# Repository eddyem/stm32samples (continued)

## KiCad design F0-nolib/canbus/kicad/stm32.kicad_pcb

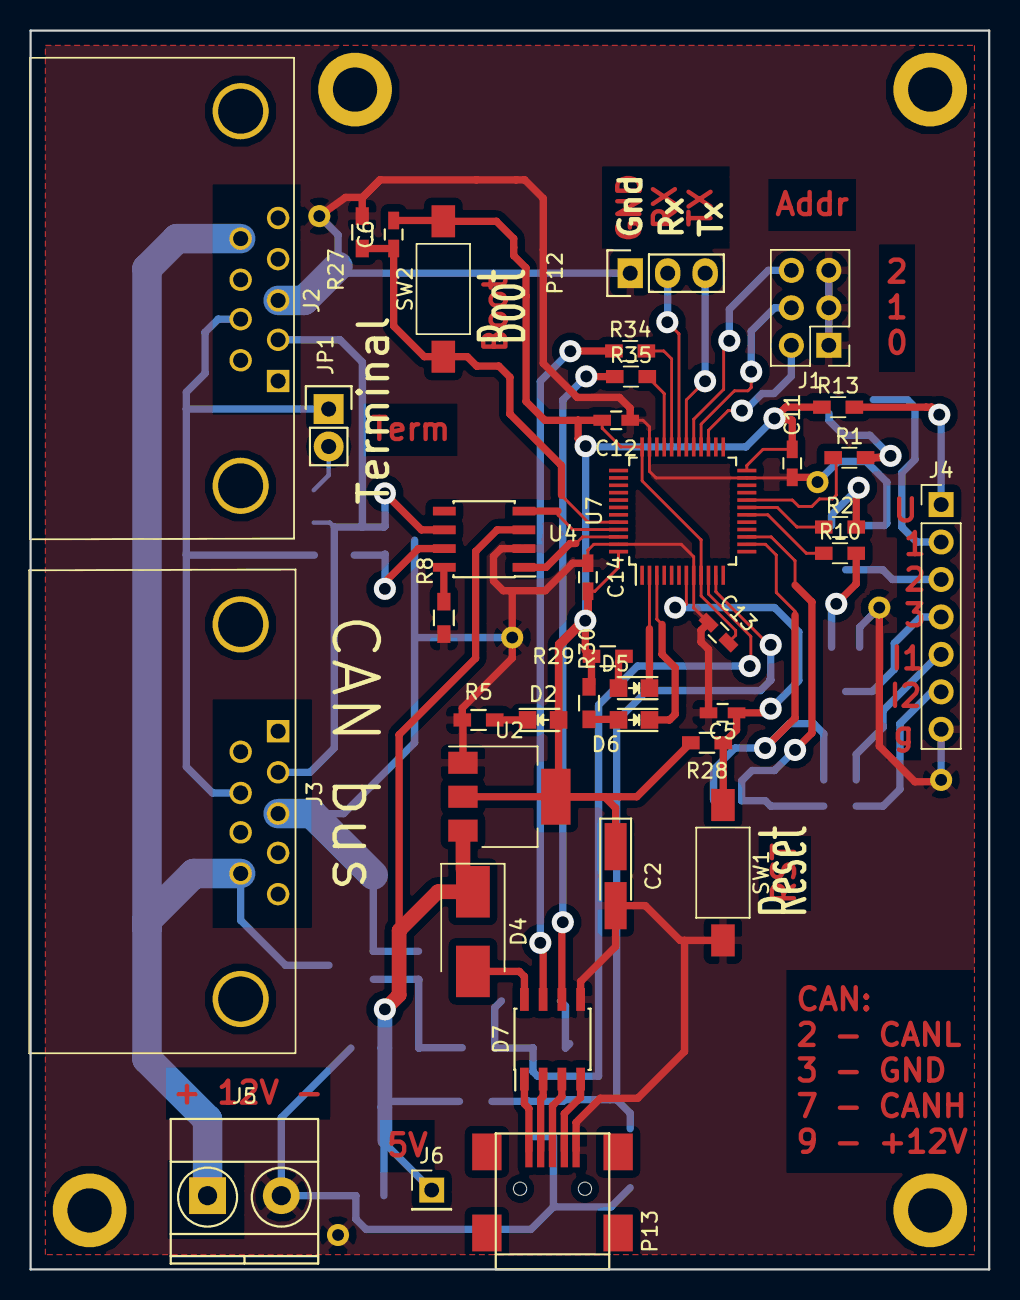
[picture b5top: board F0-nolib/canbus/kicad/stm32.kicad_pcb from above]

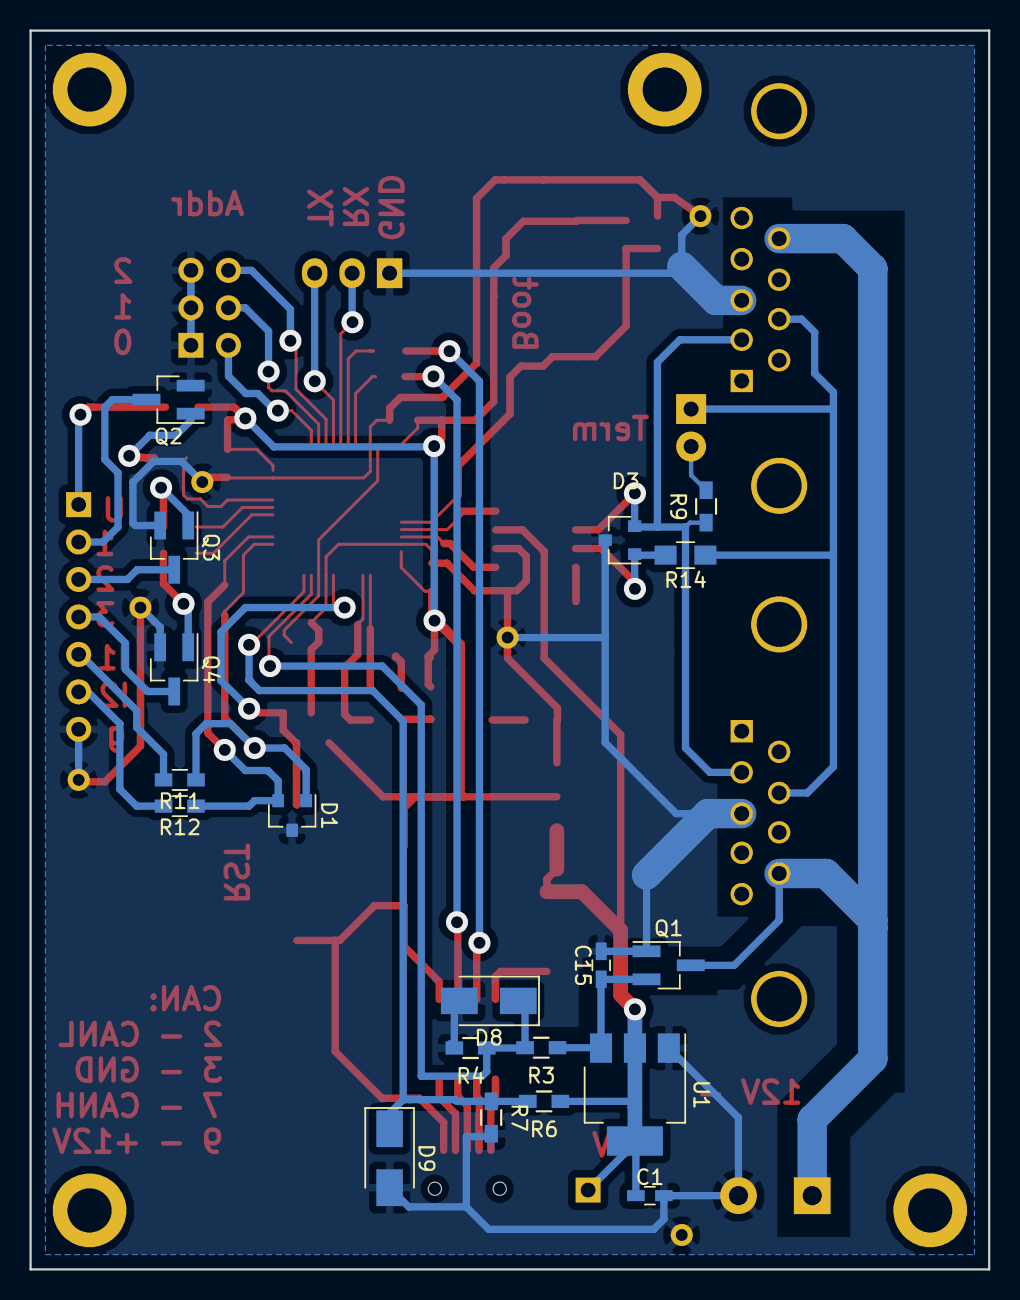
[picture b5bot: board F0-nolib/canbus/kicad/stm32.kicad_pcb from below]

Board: 2 copper layers, 65.0 x 84.0 mm, 61 parts (19 on the bottom side), 49 nets.

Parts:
C1, C5, C6, C11, C12, C13, C14, C15: 0.1; C_0603_HandSoldering
C2: 47u; Tantalum_Case-A_EIA-3216-18_Hand
D1: SP0502BAHT; SOT-23
D2: LED; LED_0805
D3: PESD1CAN; SOT-23
D4: MBRS130L; D_SMB_Handsoldering
D5: LED0; LED_0805
D6: LED1; LED_0805
D7: USB6B1; SOIC-8_3.9x4.9mm_Pitch1.27mm
D8, D9: SMAJ5.0A; D_SMA
J1: CONN_02X03; Pin_Header_Straight_2x03_Pitch2.54mm
J2: DB9_Female; DB9FC
J3: DB9_Male; DB9MC
J4: Conn_01x07; Pin_Header_Straight_1x07_Pitch2.54mm
J5: 12v; TerminalBlock_Pheonix_MKDS1.5-2pol
J6: Conn_01x01; Pin_Header_Straight_1x01_Pitch2.54mm
JP1: Terminal; Pin_Header_Straight_1x02
P12: USART_BOOT; Pin_Header_Straight_1x03
P13: USB_A; USB_Mini-B
P15, P16, P17, P18: Hole; Hole_3mm
Q1: AO3407; SOT-23_Handsoldering
Q2, Q3, Q4: SI2300; SOT-23_Handsoldering
R1, R2, R5, R10, R11, R12, R29, R30: 330; R_0603_HandSoldering
R3: 220k; R_0603_HandSoldering
R4: 56k; R_0603_HandSoldering
R6, R7: 47k; R_0603_HandSoldering
R8: 4k7; R_0603_HandSoldering
R9: 120; R_0603_HandSoldering
R13: 4.7; R_0603_HandSoldering
R14: 0; R_0805_HandSoldering
R27, R28: 10k; R_0603_HandSoldering
R34, R35: 22; R_0603_HandSoldering
SW1: Reset; SW_SPST_FSMSM
SW2: Boot; SW_SPST_FSMSM
U1: LM1117-5.0; SOT-223
U2: LM1117-3.3; SOT-223
U4: MCP2551-I/SN; SOIC-8_3.9x4.9mm_Pitch1.27mm
U7: STM32F042C6Tx; LQFP-48_7x7mm_Pitch0.5mm

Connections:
+3V3: C2.1, C6.2, C11.2, C12.2, C13.2, C14.2, D2.2, R13.1, R28.2, R29.2, R30.2, SW2.2, U2.2, U2.4, U7.9, U7.24, U7.36, U7.48
+5V: C1.1, D4.1, J6.1, R6.1, U1.2, U1.4, U2.3, U4.3
/5Vusb: D4.2, D7.8
/12Vin: C15.1, Q1.2, R3.1, U1.3
/BOOT0: C6.1, R27.1, SW2.1, U7.44
/CAN_Rx: U4.4, U7.45
/CAN_Tx: U4.1, U7.46
/INP1: D1.1, R11.1, U7.14
/INP2: D1.2, R12.1, U7.15
/LED0: D5.1, U7.2
/LED1: D6.1, U7.3
/NRST: C5.1, R28.1, SW1.1, U7.7
/O1: R1.1, U7.20
/O2: R2.1, U7.19
/O3: R10.1, U7.18
/OUTP1: J4.2, Q2.3
/OUTP2: J4.3, Q3.3
/OUTP3: J4.4, Q4.3
/Rx: P12.2, U7.31
/Tx: P12.3, U7.30
/V5: D9.1, R6.2, R7.1, U7.11
/V12: D8.1, R3.2, R4.1, U7.10
/brdaddr0: J1.2, U7.27
/brdaddr1: J1.4, U7.28
/brdaddr2: J1.6, U7.29
GND: C1.2, C2.2, C5.2, C11.1, C12.1, C13.1, C14.1, C15.2, D1.3, D3.3, D7.5, D8.2, D9.2, J1.1, J1.3, J1.5, J2.3, J3.3, J4.7, J5.2, P12.1, P13.5, Q1.1, Q2.2, Q3.2, Q4.2, R4.2, R5.1, R7.2, R8.2, R27.2, SW1.2, U1.1, U2.1, U4.2, U7.8, U7.23, U7.35, U7.47
unnamed: D2.1, R5.2
unnamed: D3.1, R14.2, U4.7
unnamed: D3.2, J2.2, J3.2, R9.1, U4.6
unnamed: D5.2, R29.1
unnamed: D6.2, R30.1
unnamed: D7.1, P13.1
unnamed: D7.2, P13.2
unnamed: D7.3, P13.3
unnamed: D7.4, P13.4
unnamed: D7.6, R35.1
unnamed: D7.7, R34.1
unnamed: J2.7, J3.7, JP1.1, R14.1
unnamed: J2.9, J3.9, J5.1, Q1.3
unnamed: J4.1, R13.2
unnamed: J4.5, R11.2
unnamed: J4.6, R12.2
unnamed: JP1.2, R9.2
unnamed: Q2.1, R1.2
unnamed: Q3.1, R2.2
unnamed: Q4.1, R10.2
unnamed: R8.1, U4.8
unnamed: R34.2, U7.32
unnamed: R35.2, U7.33

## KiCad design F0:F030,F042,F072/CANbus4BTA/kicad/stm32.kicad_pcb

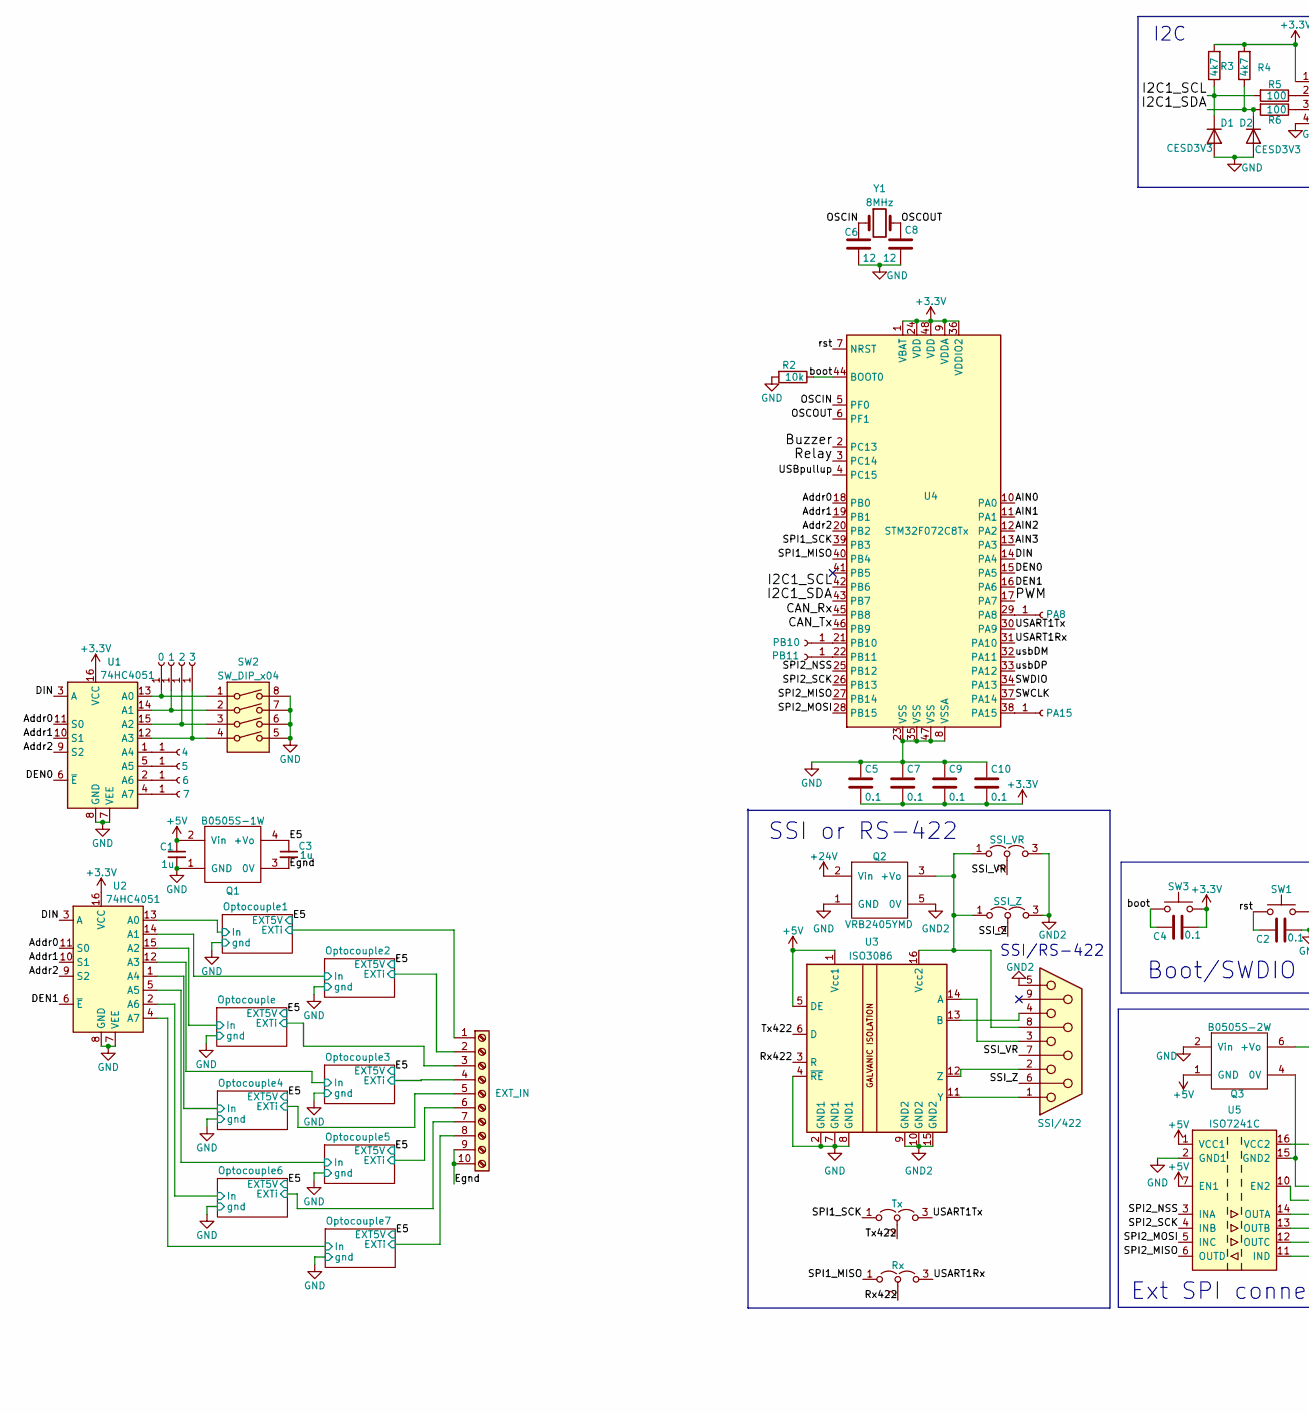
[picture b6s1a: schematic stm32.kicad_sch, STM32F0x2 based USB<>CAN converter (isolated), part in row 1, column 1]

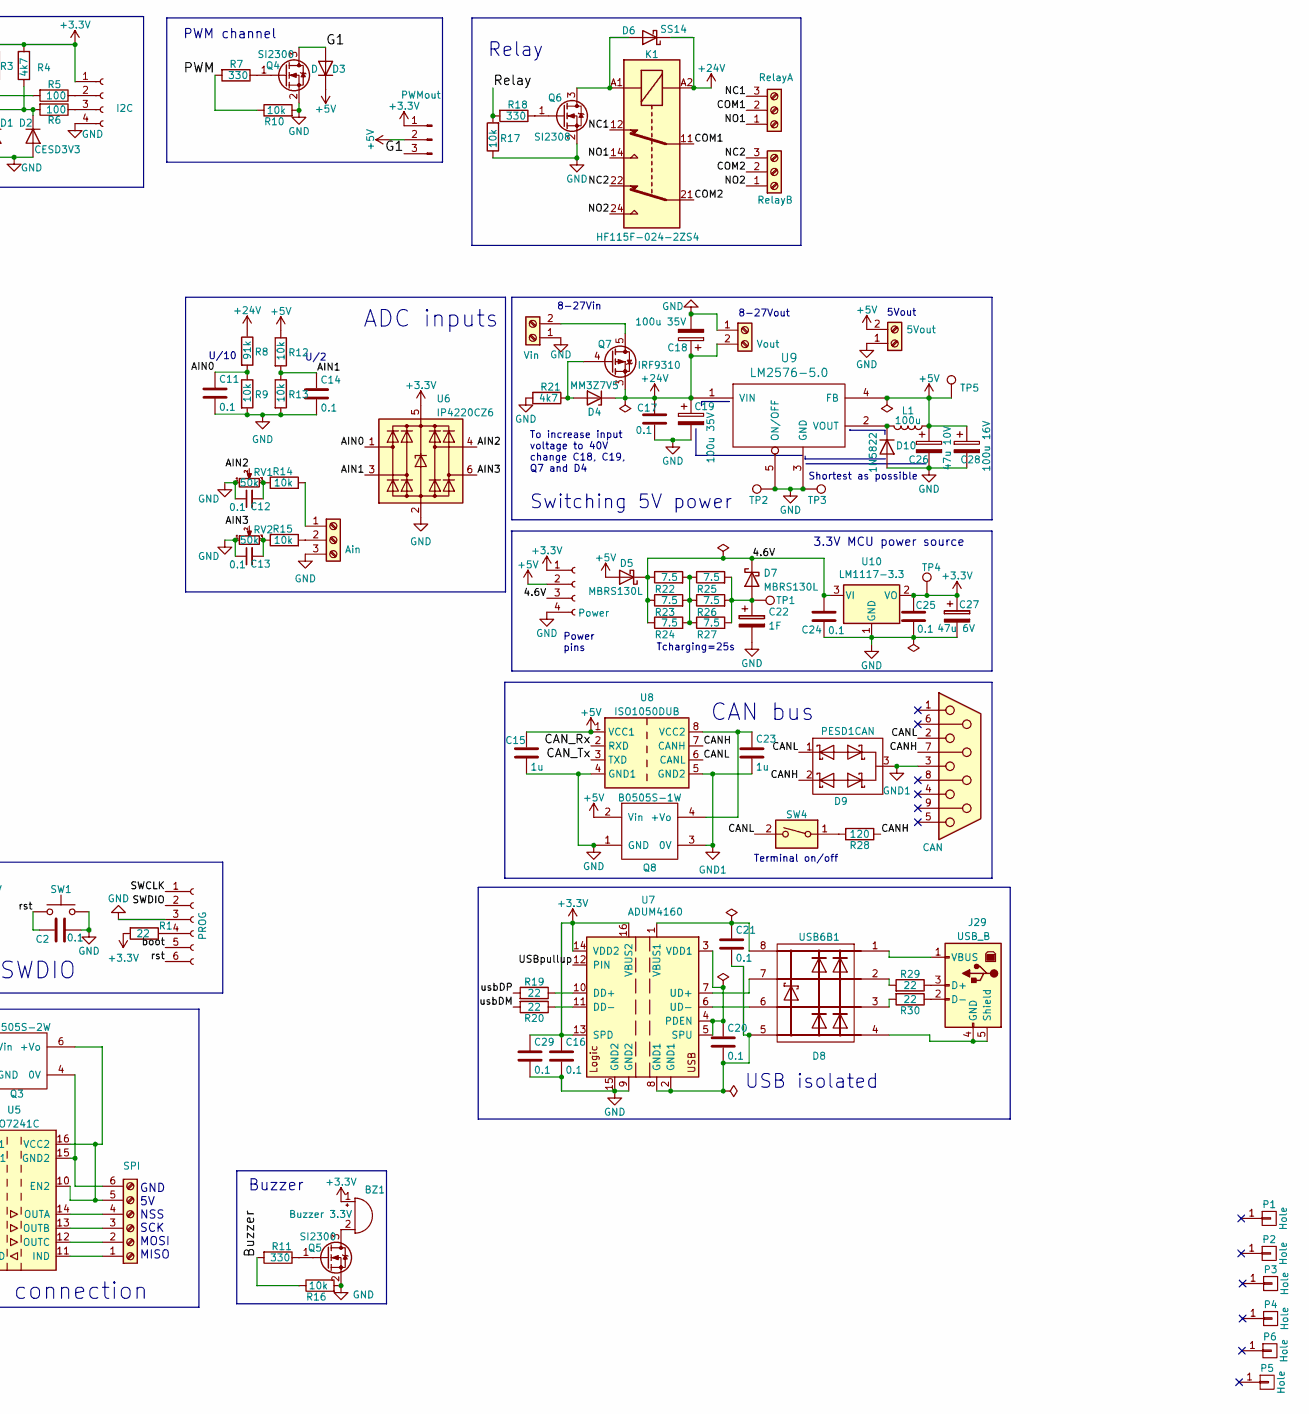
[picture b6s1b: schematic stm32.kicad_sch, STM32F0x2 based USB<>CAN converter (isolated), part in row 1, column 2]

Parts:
BZ1: Buzzer 3.3V; Buzzer_12x9.5RM7.6
C1, C3, C15, C23: 1u; C_0805_2012Metric_Pad1.18x1.45mm_HandSolder
C2, C4, C5, C7, C9, C10, C11, C12, C13, C14, C16, C17, C20, C21, C24, C25, C29: 0.1; C_0603_1608Metric_Pad1.08x0.95mm_HandSolder
C6, C8: 12; C_0603_1608Metric_Pad1.08x0.95mm_HandSolder
C18, C19: 100u 35V; CP_Radial_D8.0mm_P3.50mm
C22: 1F; C_Rect_L18.0mm_W8.0mm_P15.00mm_FKS3_FKP3
C26: 47u 10V; CP_EIA-6032-28_Kemet-C_Pad2.25x2.35mm_HandSolder
C27: 47u 6V; CP_EIA-3216-18_Kemet-A_Pad1.58x1.35mm_HandSolder
C28: 100u 16V; CP_Radial_D8.0mm_P3.50mm
D1, D2: CESD3V3; D_0805_2012Metric_Pad1.15x1.40mm_HandSolder
D3: D; D_0805_2012Metric_Pad1.15x1.40mm_HandSolder
D4: MM3Z7V5; D_0805_2012Metric_Pad1.15x1.40mm_HandSolder
D5, D7: MBRS130L; D_SMB_Handsoldering
D6: SS14; D_SMA-SMB_Universal_Handsoldering
D8: USB6B1; SOIC-8_3.9x4.9mm_P1.27mm
D9: PESD1CAN; SOT-23
D10: 1N5822; D_DO-201_P3.81mm_Vertical_AnodeUp
J1: 0; PinSocket_1x01_P2.54mm_Vertical
J2: 1; PinSocket_1x01_P2.54mm_Vertical
J3: 4; PinSocket_1x01_P2.54mm_Vertical
J4: 5; PinSocket_1x01_P2.54mm_Vertical
J5: 6; PinSocket_1x01_P2.54mm_Vertical
J6: 7; PinSocket_1x01_P2.54mm_Vertical
J7: 2; PinSocket_1x01_P2.54mm_Vertical
J8: 3; PinSocket_1x01_P2.54mm_Vertical
J9: PROG; PinSocket_1x06_P1.27mm_Vertical
J10: RelayB; TerminalBlock_Phoenix_MKDS-1,5-3_1x03_P5.00mm_Horizontal
J15: PB10; PinSocket_1x01_P2.54mm_Vertical
J16: PB11; PinSocket_1x01_P2.54mm_Vertical
J17: PA15; PinSocket_1x01_P2.54mm_Vertical
J18: SSI/422; DSUB-9_Female_Horizontal_P2.77x2.84mm_EdgePinOffset4.94mm_H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
J19: I2C; JST_PH_B4B-PH-K_1x04_P2.00mm_Vertical
J20: SPI; TerminalBlock_Phoenix_MKDS-1,5-6_1x06_P5.00mm_Horizontal
J21: Ain; TerminalBlock_Phoenix_MKDS-1,5-3_1x03_P5.00mm_Horizontal
J22: PWMout; JST_PH_B3B-PH-K_1x03_P2.00mm_Vertical
J23: Vin; TerminalBlock_Phoenix_MKDS-1,5-2_1x02_P5.00mm_Horizontal
J24: Power; JST_PH_B4B-PH-K_1x04_P2.00mm_Vertical
J25: RelayA; TerminalBlock_Phoenix_MKDS-1,5-3_1x03_P5.00mm_Horizontal
J26: Vout; TerminalBlock_Phoenix_MKDS-1,5-2_1x02_P5.00mm_Horizontal
J27: 5Vout; TerminalBlock_Phoenix_MKDS-1,5-2_1x02_P5.00mm_Horizontal
J28: CAN; DSUB-9_Female_Horizontal_P2.77x2.84mm_EdgePinOffset4.94mm_H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
J29: USB_B; USB_B_OST_USB-B1HSxx_Horizontal
J30: EXT_IN; PhoenixContact_MC_1,5_10-GF-5.08_1x10_P5.08mm_Horizontal_Th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
J38: PA8; PinSocket_1x01_P2.54mm_Vertical
JP1: Tx; PinHeader_1x03_P2.54mm_Vertical
JP2: Rx; PinHeader_1x03_P2.54mm_Vertical
JP3: SSI_VR; PinHeader_1x03_P2.54mm_Vertical
JP4: SSI_Z; PinHeader_1x03_P2.54mm_Vertical
K1: HF115F-024-2ZS4; Relay_DPDT_Finder_40.52
L1: 100u; L_Toroid_Horizontal_D6.5mm_P10.00mm_Diameter7-5mm_Amidon-T25
P1, P2, P3, P4, P5, P6: Hole; Hole_3mm
Q1, Q8: B0505S-1W; B0x0xS
Q2: VRB2405YMD; VRB2405
Q3: B0505S-2W
Q4, Q5: SI2300; SOT-23_Handsoldering
Q6: SI2308; SOT-23_Handsoldering
Q7: IRF9310; SO-8_3.9x4.9mm_P1.27mm
R1, R19, R20, R29, R30: 22; R_0603_1608Metric_Pad0.98x0.95mm_HandSolder
R2, R9, R10, R12, R13, R14, R15, R16, R17: 10k; R_0603_1608Metric_Pad0.98x0.95mm_HandSolder
R3, R4, R21: 4k7; R_0603_1608Metric_Pad0.98x0.95mm_HandSolder
R5, R6: 100; R_0603_1608Metric_Pad0.98x0.95mm_HandSolder
R7, R11, R18: 330; R_0603_1608Metric_Pad0.98x0.95mm_HandSolder
R8: 91k; R_0603_1608Metric_Pad0.98x0.95mm_HandSolder
R22, R23, R24, R25, R26, R27: 7.5; R_2010_5025Metric_Pad1.40x2.65mm_HandSolder
R28: 120; R_1210_3225Metric_Pad1.30x2.65mm_HandSolder
RV1, RV2: 50k; Potentiometer_Bourns_3296W_Vertical
SW1, SW3: SW_Push; SW_SPST_FSMSM
SW2: SW_DIP_x04; SW_DIP_SPSTx04_Slide_9.78x12.34mm_W7.62mm_P2.54mm
SW4: SW_DIP_x01; SW_DIP_SPSTx01_Slide_6.7x4.1mm_W7.62mm_P2.54mm_LowProfile
TP1: 4.6V; PinSocket_1x01_P2.54mm_Vertical
TP2, TP3: Gnd; PinSocket_1x01_P2.54mm_Vertical
TP4: 3.3V; PinSocket_1x01_P2.54mm_Vertical
TP5: 5V; PinSocket_1x01_P2.54mm_Vertical
U1, U2: 74HC4051; SOIC-16_3.9x9.9mm_P1.27mm
U3: ISO3086; SOIC-16W_7.5x10.3mm_P1.27mm
U4: STM32F072C8Tx; LQFP-48_7x7mm_P0.5mm
U5: ISO7241C; SOIC-16W_7.5x10.3mm_P1.27mm
U6: IP4220CZ6; SOT-23-6
U7: ADUM4160; SOIC-16W_7.5x10.3mm_P1.27mm
U8: ISO1050DUB; SOP-8_6.62x9.15mm_P2.54mm
U9: LM2576-5.0; TO-220-5_P3.4x3.7mm_StaggerEven_Lead3.8mm_Vertical
U10: LM1117-3.3; SOT-223-3_TabPin2
Y1: 8MHz; Crystal_HC49-U_Vertical

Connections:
+3.3V: BZ1.1 (-), C4.2, C5.2, C7.2, C9.2, C10.2, C16.1, C25.1, C27.1, C29.1, J19.1, J22.1, J24.1, R1.2, R3.2, R4.2, SW3.2, TP4.1, U1.16 (VCC), U2.16 (VCC), U4.1 (VBAT), U4.9 (VDDA), U4.24 (VDD), U4.36 (VDDIO2), U4.48 (VDD), U6.5 (VBUS), U7.13 (SPD), U7.14 (VDD2), U7.16 (VBUS2), U10.2 (VO)
+5V: C1.1, C15.1, C26.1, C28.1, D3.1 (K), D5.2 (A), J22.2, J24.2, J27.2, L1.1, Q1.2 (Vin), Q3.1 (GND), Q8.2 (Vin), R12.1, TP5.1, U3.1 (Vcc1), U3.5 (DE), U5.1 (VCC1), U5.7 (EN1), U8.1 (VCC1), U9.4 (FB)
+24V: C17.1, C18.1, C19.1, D4.1 (K), D6.1 (K), J26.2, K1.A2, Q2.2 (Vin), Q7.1 (S), Q7.2 (S), Q7.3 (S), R8.1, U9.1 (VIN)
/4.6V: C24.1, D5.1 (K), D7.1 (K), J24.3, R22.1, R23.1, R24.1, U10.3 (VI)
/AIN0: C11.1, R8.2, R9.1, U4.10 (PA0), U6.1 (I/O1)
/AIN1: C14.1, R12.2, R13.1, U4.11 (PA1), U6.3 (I/O2)
/AIN2: RV1.2, U4.12 (PA2), U6.4 (I/O3)
/AIN3: RV2.2, U4.13 (PA3), U6.6 (I/O4)
/Addr0: U1.11 (S0), U2.11 (S0), U4.18 (PB0)
/Addr1: U1.10 (S1), U2.10 (S1), U4.19 (PB1)
/Addr2: U1.9 (S2), U2.9 (S2), U4.20 (PB2)
/Buzzer: R11.2, R16.1, U4.2 (PC13)
/CANH: D9.2 (K), J28.7, R28.1, U8.7 (CANH)
/CANL: D9.1 (K), J28.2, SW4.2, U8.6 (CANL)
/CAN_Rx: U4.45 (PB8), U8.2 (RXD)
/CAN_Tx: U4.46 (PB9), U8.3 (TXD)
/COM1: J25.2, K1.11
/COM2: J10.2, K1.21
/DEN0: U1.6 (~E), U4.15 (PA5)
/DEN1: U2.6 (~E), U4.16 (PA6)
/DIN: U1.3 (A), U2.3 (A), U4.14 (PA4)
/E5: C3.1, Q1.4 (+Vo); also elsewhere on the board
/Egnd: C3.2, J30.9, J30.10, Q1.3 (0V)
/G1: D3.2 (A), J22.3, Q4.3 (D)
/I2C1_SCL: D1.1 (K), R3.1, R5.2, U4.42 (PB6)
/I2C1_SDA: D2.1 (K), R4.1, R6.2, U4.43 (PB7)
/NC1: J25.3, K1.12
/NC2: J10.3, K1.22
/NO1: J25.1, K1.14
/NO2: J10.1, K1.24
/OSCIN: C6.1, U4.5 (PF0), Y1.1
/OSCOUT: C8.1, U4.6 (PF1), Y1.2
/Optocouple1/EXTi: J30.1; also elsewhere on the board
/Optocouple1/In: U2.13 (A0); also elsewhere on the board
/Optocouple2/EXTi: J30.2; also elsewhere on the board
/Optocouple2/In: U2.14 (A1); also elsewhere on the board
/Optocouple3/EXTi: J30.4; also elsewhere on the board
/Optocouple3/In: U2.12 (A3); also elsewhere on the board
/Optocouple4/EXTi: J30.5; also elsewhere on the board
/Optocouple4/In: U2.1 (A4); also elsewhere on the board
/Optocouple5/EXTi: J30.6; also elsewhere on the board
/Optocouple5/In: U2.5 (A5); also elsewhere on the board
/Optocouple6/EXTi: J30.7; also elsewhere on the board
/Optocouple6/In: U2.2 (A6); also elsewhere on the board
/Optocouple7/EXTi: J30.8; also elsewhere on the board
/Optocouple7/In: U2.4 (A7); also elsewhere on the board
/Optocouple/EXTi: J30.3; also elsewhere on the board
/Optocouple/In: U2.15 (A2); also elsewhere on the board
/PWM: R7.2, R10.1, U4.17 (PA7)
/Relay: R17.2, R18.2, U4.3 (PC14)
/Rx422: JP2.2 (C), U3.3 (R)
/SPI1_MISO: JP2.1 (A), U4.40 (PB4)
/SPI1_SCK: JP1.1 (A), U4.39 (PB3)
/SPI2_MISO: U4.27 (PB14), U5.6 (OUTD)
/SPI2_MOSI: U4.28 (PB15), U5.5 (INC)
/SPI2_NSS: U4.25 (PB12), U5.3 (INA)
/SPI2_SCK: U4.26 (PB13), U5.4 (INB)
/SSI_VR: J18.7, JP3.2 (C)
/SSI_Z: J18.6, JP4.2 (C)
/SWCLK: J9.1, U4.37 (PA14)
/SWDIO: J9.2, U4.34 (PA13)
/Tx422: JP1.2 (C), U3.6 (D)
/USART1Rx: JP2.3 (B), U4.31 (PA10)
/USART1Tx: JP1.3 (B), U4.30 (PA9)
/USBpullup: U4.4 (PC15), U7.12 (PIN)
/boot: C4.1, J9.5, R2.1, SW3.1, U4.44 (BOOT0)
/rst: C2.1, J9.6, SW1.1, U4.7 (NRST)
/usbDM: R20.2, U4.32 (PA11)
/usbDP: R19.2, U4.33 (PA12)
GND: C1.2, C2.2, C5.1, C6.2, C7.1, C8.2, C9.1, C10.1, C11.2, C12.1, C13.1, C14.2, C15.2, C16.2, C17.2, C18.2, C19.2, C22.2, C24.2, C25.2, C26.2, C27.2, C28.2, C29.2, D1.2 (A), D2.2 (A), D10.2 (A), J9.3, J19.4, J21.3, J23.1, J24.4, J26.1, J27.1, Q1.1 (GND), Q2.1 (GND), Q3.2 (Vin), Q4.2 (S), Q5.2 (S), Q6.2 (S), Q8.1 (GND), R2.2, R9.2, R10.2, R13.2, R16.2, R17.1, R21.2, RV1.1, RV2.1, SW1.2, SW2.5, SW2.6, SW2.7, SW2.8, TP2.1, TP3.1, U1.7 (VEE), U1.8 (GND), U2.7 (VEE), U2.8 (GND), U3.2 (GND1), U3.4 (~RE), U3.7 (GND1), U3.8 (GND1), U4.8 (VSSA), U4.23 (VSS), U4.35 (VSS), U4.47 (VSS), U5.2 (GND1), U5.8 (GND1), U6.2 (GND), U7.9 (GND2), U7.15 (GND2), U8.4 (GND1), U9.3 (GND), U9.5 (ON/OFF), U10.1 (GND); also elsewhere on the board
GND1: C23.2, D9.3 (O), J28.3, Q8.3 (0V), U8.5 (GND2)
GND2: J18.5, JP3.3 (B), JP4.3 (B), Q2.5 (0V), U3.9 (GND2), U3.10 (GND2), U3.15 (GND2)
unnamed: BZ1.2 (+), Q5.3 (D)
unnamed: C12.2, R14.1, RV1.3
unnamed: C13.2, R15.1, RV2.3
unnamed: C20.1, U7.3 (VDD1), U7.4 (PDEN), U7.5 (SPU)
unnamed: C20.2, C21.2, D8.5 (GND), U7.2 (GND1), U7.8 (GND1)
unnamed: C21.1, D8.8 (VCC), U7.1 (VBUS1)
unnamed: C22.1, D7.2 (A), R25.2, R26.2, R27.2, TP1.1
unnamed: C23.1, Q8.4 (+Vo), U8.8 (VCC2)
unnamed: D4.2 (A), Q7.4 (G), R21.1
unnamed: D6.2 (A), K1.A1, Q6.3 (D)
unnamed: D8.1 (VCC), J29.1 (VBUS)
unnamed: D8.2 (I/O1), R29.2
unnamed: D8.3 (I/O2), R30.2
unnamed: D8.4 (GND), J29.4 (GND), J29.5 (Shield)
unnamed: D8.6 (I/O2), U7.6 (UD-)
unnamed: D8.7 (I/O1), U7.7 (UD+)
unnamed: D10.1 (K), L1.2, U9.2 (VOUT)
unnamed: J1.1, SW2.1, U1.13 (A0)
unnamed: J2.1, SW2.2, U1.14 (A1)
unnamed: J3.1, U1.1 (A4)
unnamed: J4.1, U1.5 (A5)
unnamed: J5.1, U1.2 (A6)
unnamed: J6.1, U1.4 (A7)
unnamed: J7.1, SW2.3, U1.15 (A2)
unnamed: J8.1, SW2.4, U1.12 (A3)
unnamed: J9.4, R1.1
unnamed: J15.1, U4.21 (PB10)
unnamed: J16.1, U4.22 (PB11)
unnamed: J17.1, U4.38 (PA15)
unnamed: J18.1, U3.11 (Y)
unnamed: J18.2, U3.12 (Z)
unnamed: J18.3, U3.14 (A)
unnamed: J18.4, U3.13 (B)
unnamed: J18.8, JP3.1 (A), JP4.1 (A), Q2.3 (+Vo), U3.16 (Vcc2)
unnamed: J19.2, R5.1
unnamed: J19.3, R6.1
unnamed: J20.1, U5.11 (IND)
unnamed: J20.2, U5.12 (OUTC)
unnamed: J20.3, U5.13 (OUTB)
unnamed: J20.4, U5.14 (OUTA)
unnamed: J20.5, Q3.6 (+Vo), U5.10 (EN2), U5.16 (VCC2)
unnamed: J20.6, Q3.4 (0V), U5.9 (GND2), U5.15 (GND2)
unnamed: J21.1, R14.2
unnamed: J21.2, R15.2
unnamed: J23.2, Q7.5 (D), Q7.6 (D), Q7.7 (D), Q7.8 (D)
unnamed: J29.2 (D-), R30.1
unnamed: J29.3 (D+), R29.1
unnamed: J38.1, U4.29 (PA8)
unnamed: Q4.1 (G), R7.1
unnamed: Q5.1 (G), R11.1
unnamed: Q6.1 (G), R18.1
unnamed: R19.1, U7.10 (DD+)
unnamed: R20.1, U7.11 (DD-)
unnamed: R22.2, R23.2, R24.2, R25.1, R26.1, R27.1
unnamed: R28.2, SW4.1

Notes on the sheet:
8-27Vout
U/2
Switching 5V power
PWM channel
Buzzer
Shortest as possible
CAN bus
U/10
USB isolated
To increase input voltage to 40V change C18, C19, Q7 and D4
GND 5V NSS SCK MOSI MISO
Boot/SWDIO
3.3V MCU power source
Ext SPI connection
8-27Vin
Tcharging=25s
I2C
ADC inputs
Power pins
5Vout
Terminal on/off
Relay
SSI/RS-422
SSI or RS-422

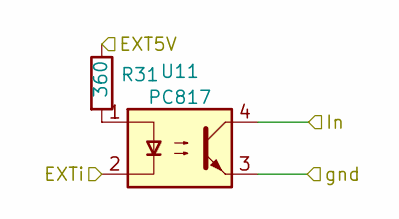
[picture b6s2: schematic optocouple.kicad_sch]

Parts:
R31: 360; R_0603_1608Metric_Pad0.98x0.95mm_HandSolder
U11: PC817; DIP-4_W7.62mm

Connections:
/E5: R31.1; also elsewhere on the board
/Optocouple/EXTi: U11.2; also elsewhere on the board
/Optocouple/In: U11.4; also elsewhere on the board
GND: U11.3; also elsewhere on the board
unnamed: R31.2, U11.1

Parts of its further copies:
R32, R33, R34, R35, R36, R37, R38: 360; R_0603_1608Metric_Pad0.98x0.95mm_HandSolder
U12, U13, U14, U15, U16, U17, U18: PC817; DIP-4_W7.62mm

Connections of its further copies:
/E5: R32.1, R33.1, R34.1, R35.1, R36.1, R37.1, R38.1; also elsewhere on the board
/Optocouple1/EXTi: U12.2; also elsewhere on the board
/Optocouple1/In: U12.4; also elsewhere on the board
/Optocouple2/EXTi: U13.2; also elsewhere on the board
/Optocouple2/In: U13.4; also elsewhere on the board
/Optocouple3/EXTi: U14.2; also elsewhere on the board
/Optocouple3/In: U14.4; also elsewhere on the board
/Optocouple4/EXTi: U15.2; also elsewhere on the board
/Optocouple4/In: U15.4; also elsewhere on the board
/Optocouple5/EXTi: U16.2; also elsewhere on the board
/Optocouple5/In: U16.4; also elsewhere on the board
/Optocouple6/EXTi: U17.2; also elsewhere on the board
/Optocouple6/In: U17.4; also elsewhere on the board
/Optocouple7/EXTi: U18.2; also elsewhere on the board
/Optocouple7/In: U18.4; also elsewhere on the board
GND: U12.3, U13.3, U14.3, U15.3, U16.3, U17.3, U18.3; also elsewhere on the board
unnamed: R32.2, U12.1
unnamed: R33.2, U13.1
unnamed: R34.2, U14.1
unnamed: R35.2, U15.1
unnamed: R36.2, U16.1
unnamed: R37.2, U17.1
unnamed: R38.2, U18.1

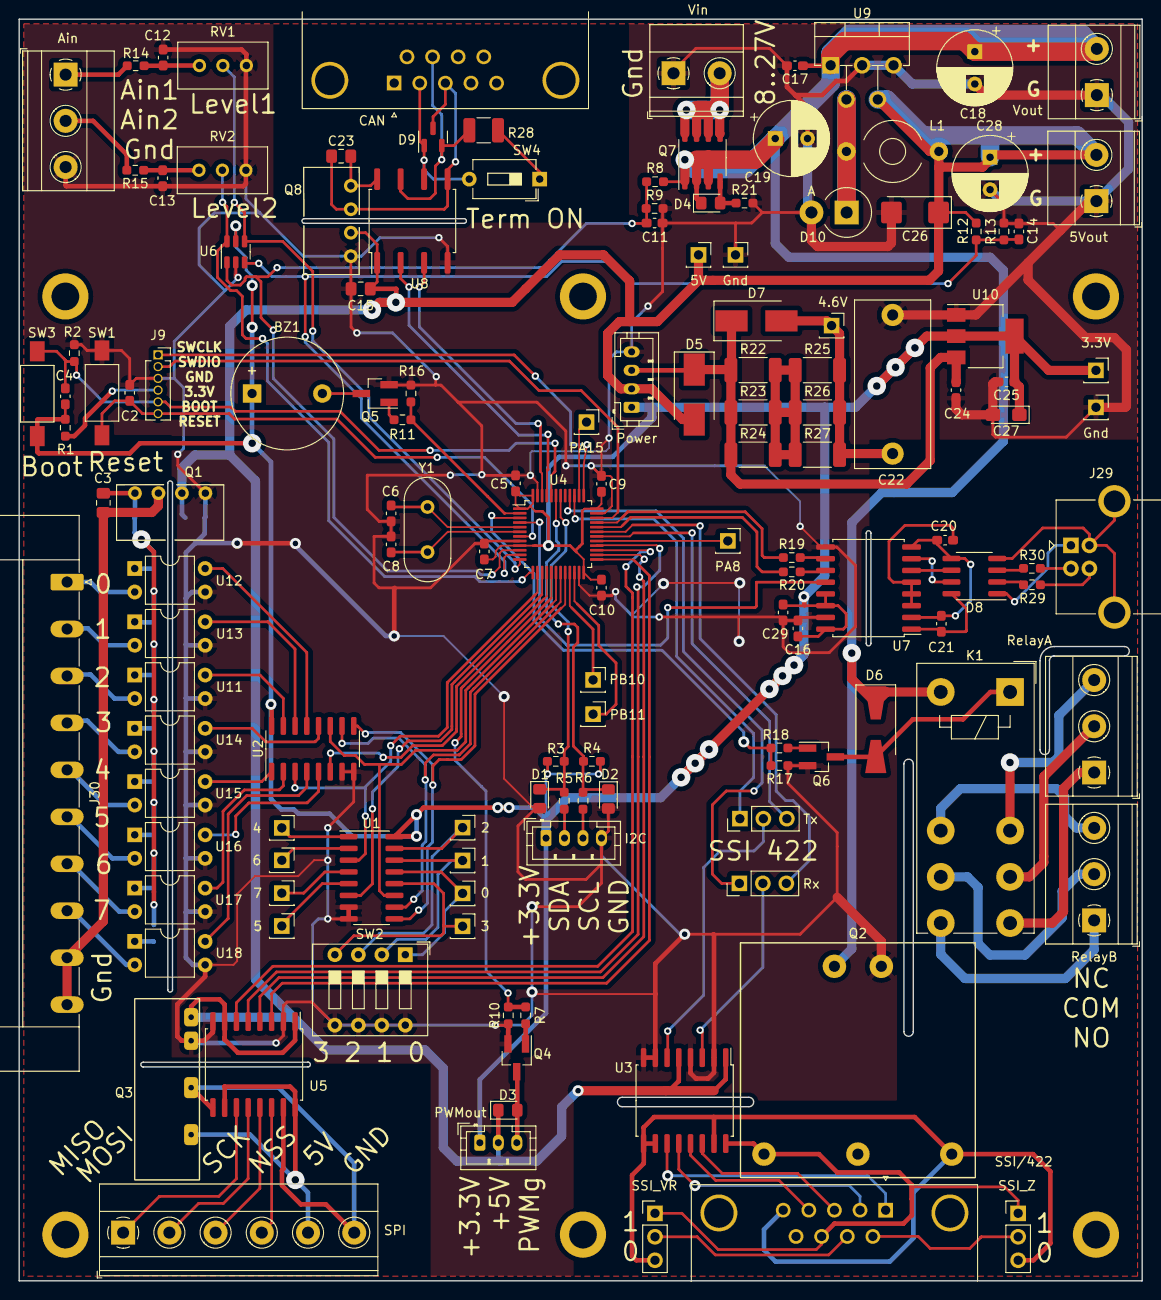
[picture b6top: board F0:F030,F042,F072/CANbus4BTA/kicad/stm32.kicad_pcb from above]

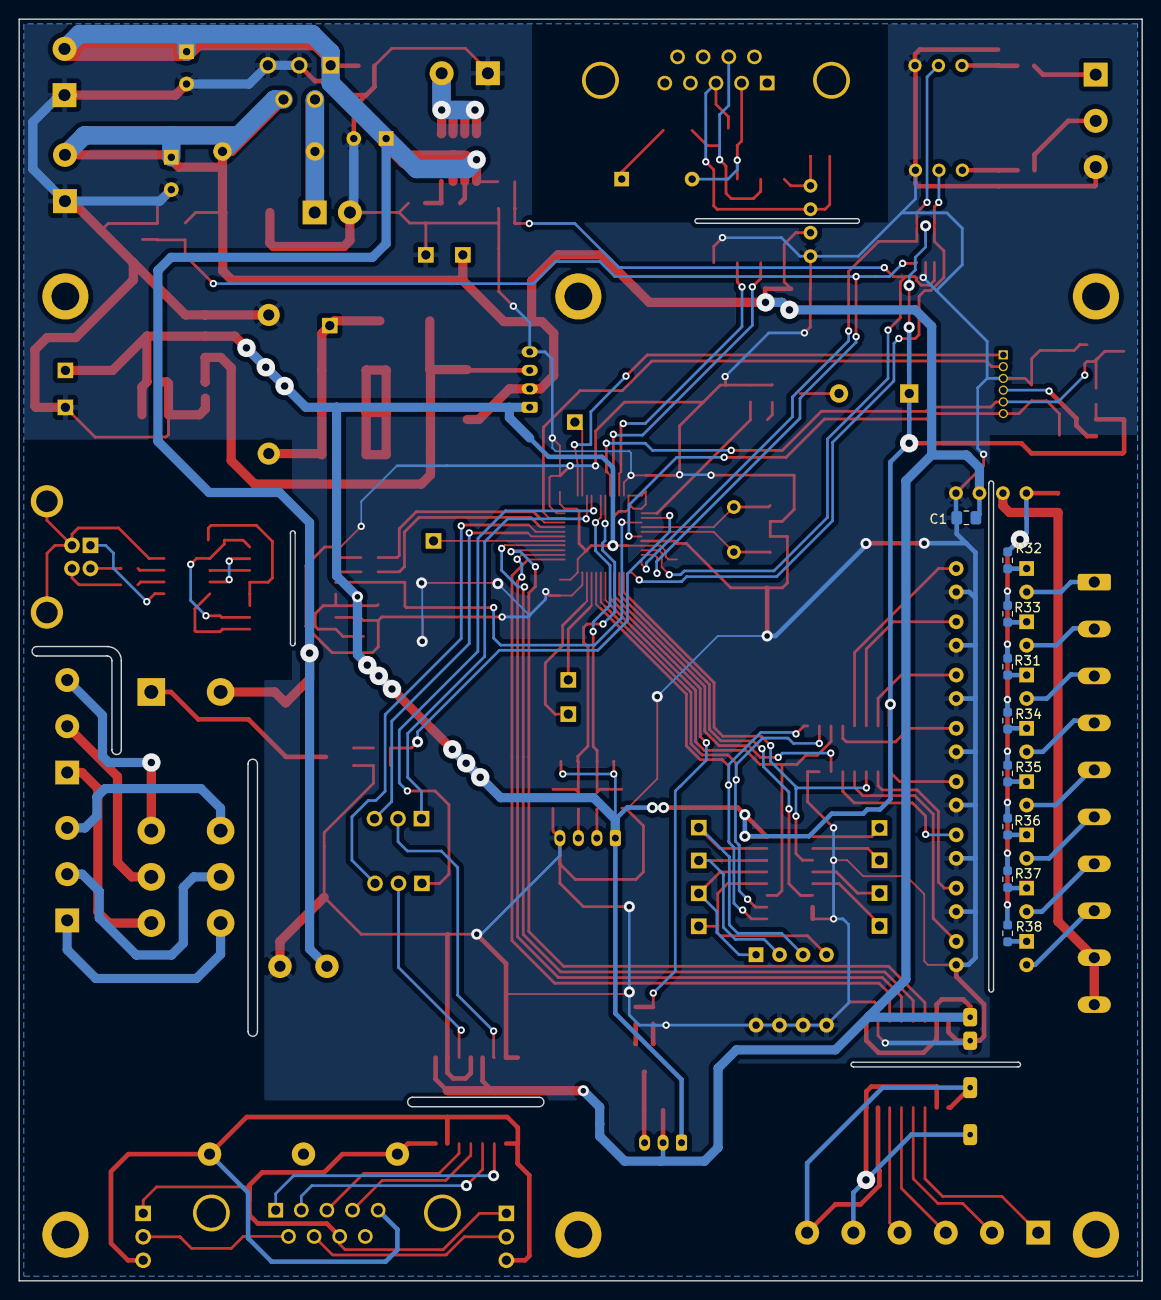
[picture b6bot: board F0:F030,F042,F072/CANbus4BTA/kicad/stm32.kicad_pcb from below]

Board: 2 copper layers, 121.5 x 136.5 mm, 155 parts (9 on the bottom side), 135 nets.
